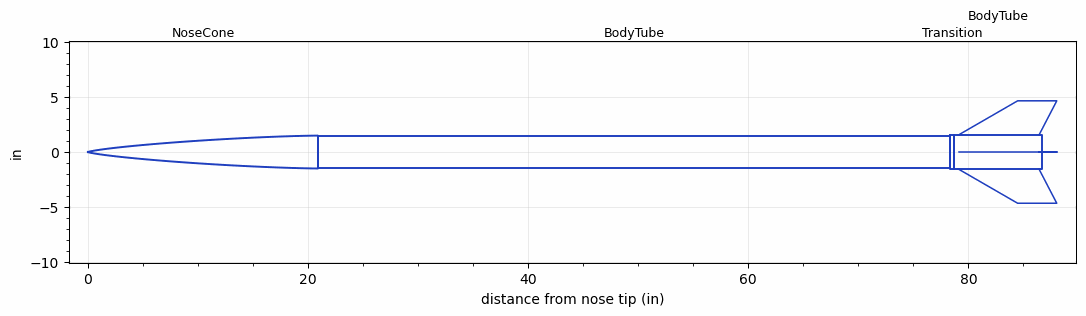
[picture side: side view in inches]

<RASAeroDocument>
 <FileVersion>2</FileVersion>
 <RocketDesign>
  <NoseCone>
   <Length>20.895</Length>
   <Diameter>2.985</Diameter>
   <Shape>Von Karman Ogive</Shape>
   <BluntRadius>0.125</BluntRadius>
   <Location>0</Location>
  </NoseCone>
  <BodyTube>
   <Length>57.445</Length>
   <Diameter>2.985</Diameter>
   <Location>20.895</Location>
  </BodyTube>
  <Transition>
   <Length>0.348</Length>
   <Diameter>3.11</Diameter>
   <Location>78.34</Location>
   <RearDiameter>3.11</RearDiameter>
  </Transition>
  <BodyTube>
   <Length>7.983</Length>
   <Diameter>3.11</Diameter>
   <Location>78.688</Location>
   <Fin>
    <Count>4</Count>
    <Chord>7.312</Chord>
    <Span>3.1</Span>
    <SweepDistance>5.369</SweepDistance>
    <TipChord>3.554</TipChord>
    <Thickness>0.1</Thickness>
    <LERadius>0.005</LERadius>
    <Location>7.562</Location>
    <AirfoilSection>Biconvex</AirfoilSection>
   </Fin>
  </BodyTube>
  <Surface>Rough Camouflage Paint</Surface>
  <ModifiedBarrowman>True</ModifiedBarrowman>
  <Turbulence>True</Turbulence>
  <UseBooster1>False</UseBooster1>
  <UseBooster2>False</UseBooster2>
 </RocketDesign>
 <LaunchSite>
  <Altitude>3900</Altitude>
  <Pressure>0</Pressure>
  <RodAngle>0.5</RodAngle>
  <RodLength>8</RodLength>
  <Temperature>70</Temperature>
  <WindSpeed>6</WindSpeed>
 </LaunchSite>
 <Recovery>
  <Altitude1>1000</Altitude1>
  <Altitude2>10000</Altitude2>
  <DeviceType1>Parachute</DeviceType1>
  <DeviceType2>Parachute</DeviceType2>
  <Event1>True</Event1>
  <Event2>True</Event2>
  <Size1>20</Size1>
  <Size2>60</Size2>
  <EventType1>Apogee</EventType1>
  <EventType2>Altitude</EventType2>
  <CD1>1.5</CD1>
  <CD2>1.2</CD2>
 </Recovery>
 <SimulationList>
  <Simulation>
   <SustainerEngine>N3100  (Jellyfish)</SustainerEngine>
   <SustainerLaunchWt>35.18</SustainerLaunchWt>
   <SustainerNozzleDiameter>2.625</SustainerNozzleDiameter>
   <SustainerCG>52.67</SustainerCG>
   <SustainerIgnitionDelay>0</SustainerIgnitionDelay>
   <Booster1SeparationDelay>0</Booster1SeparationDelay>
   <Booster1IgnitionDelay>0</Booster1IgnitionDelay>
   <IncludeBooster1>False</IncludeBooster1>
   <Booster2Delay>0</Booster2Delay>
   <IncludeBooster2>False</IncludeBooster2>
   <TimetoApogee>84.27959</TimetoApogee>
   <MaxAltitude>125654.1</MaxAltitude>
   <MaxVelocity>3970.332</MaxVelocity>
  </Simulation>
  <Simulation>
   <SustainerLaunchWt>39.11</SustainerLaunchWt>
   <SustainerNozzleDiameter>2.9</SustainerNozzleDiameter>
   <SustainerCG>53.64</SustainerCG>
   <SustainerIgnitionDelay>0</SustainerIgnitionDelay>
   <Booster1SeparationDelay>0</Booster1SeparationDelay>
   <Booster1IgnitionDelay>0</Booster1IgnitionDelay>
   <IncludeBooster1>False</IncludeBooster1>
   <Booster2Delay>0</Booster2Delay>
   <IncludeBooster2>False</IncludeBooster2>
  </Simulation>
  <Simulation>
   <SustainerLaunchWt>39.11</SustainerLaunchWt>
   <SustainerNozzleDiameter>2.9</SustainerNozzleDiameter>
   <SustainerCG>53.64</SustainerCG>
   <SustainerIgnitionDelay>0</SustainerIgnitionDelay>
   <Booster1SeparationDelay>0</Booster1SeparationDelay>
   <Booster1IgnitionDelay>0</Booster1IgnitionDelay>
   <IncludeBooster1>False</IncludeBooster1>
   <Booster2Delay>0</Booster2Delay>
   <IncludeBooster2>False</IncludeBooster2>
  </Simulation>
  <Simulation>
   <SustainerLaunchWt>39.11</SustainerLaunchWt>
   <SustainerNozzleDiameter>2.9</SustainerNozzleDiameter>
   <SustainerCG>53.64</SustainerCG>
   <SustainerIgnitionDelay>0</SustainerIgnitionDelay>
   <Booster1SeparationDelay>0</Booster1SeparationDelay>
   <Booster1IgnitionDelay>0</Booster1IgnitionDelay>
   <IncludeBooster1>False</IncludeBooster1>
   <Booster2Delay>0</Booster2Delay>
   <IncludeBooster2>False</IncludeBooster2>
  </Simulation>
 </SimulationList>
</RASAeroDocument>
